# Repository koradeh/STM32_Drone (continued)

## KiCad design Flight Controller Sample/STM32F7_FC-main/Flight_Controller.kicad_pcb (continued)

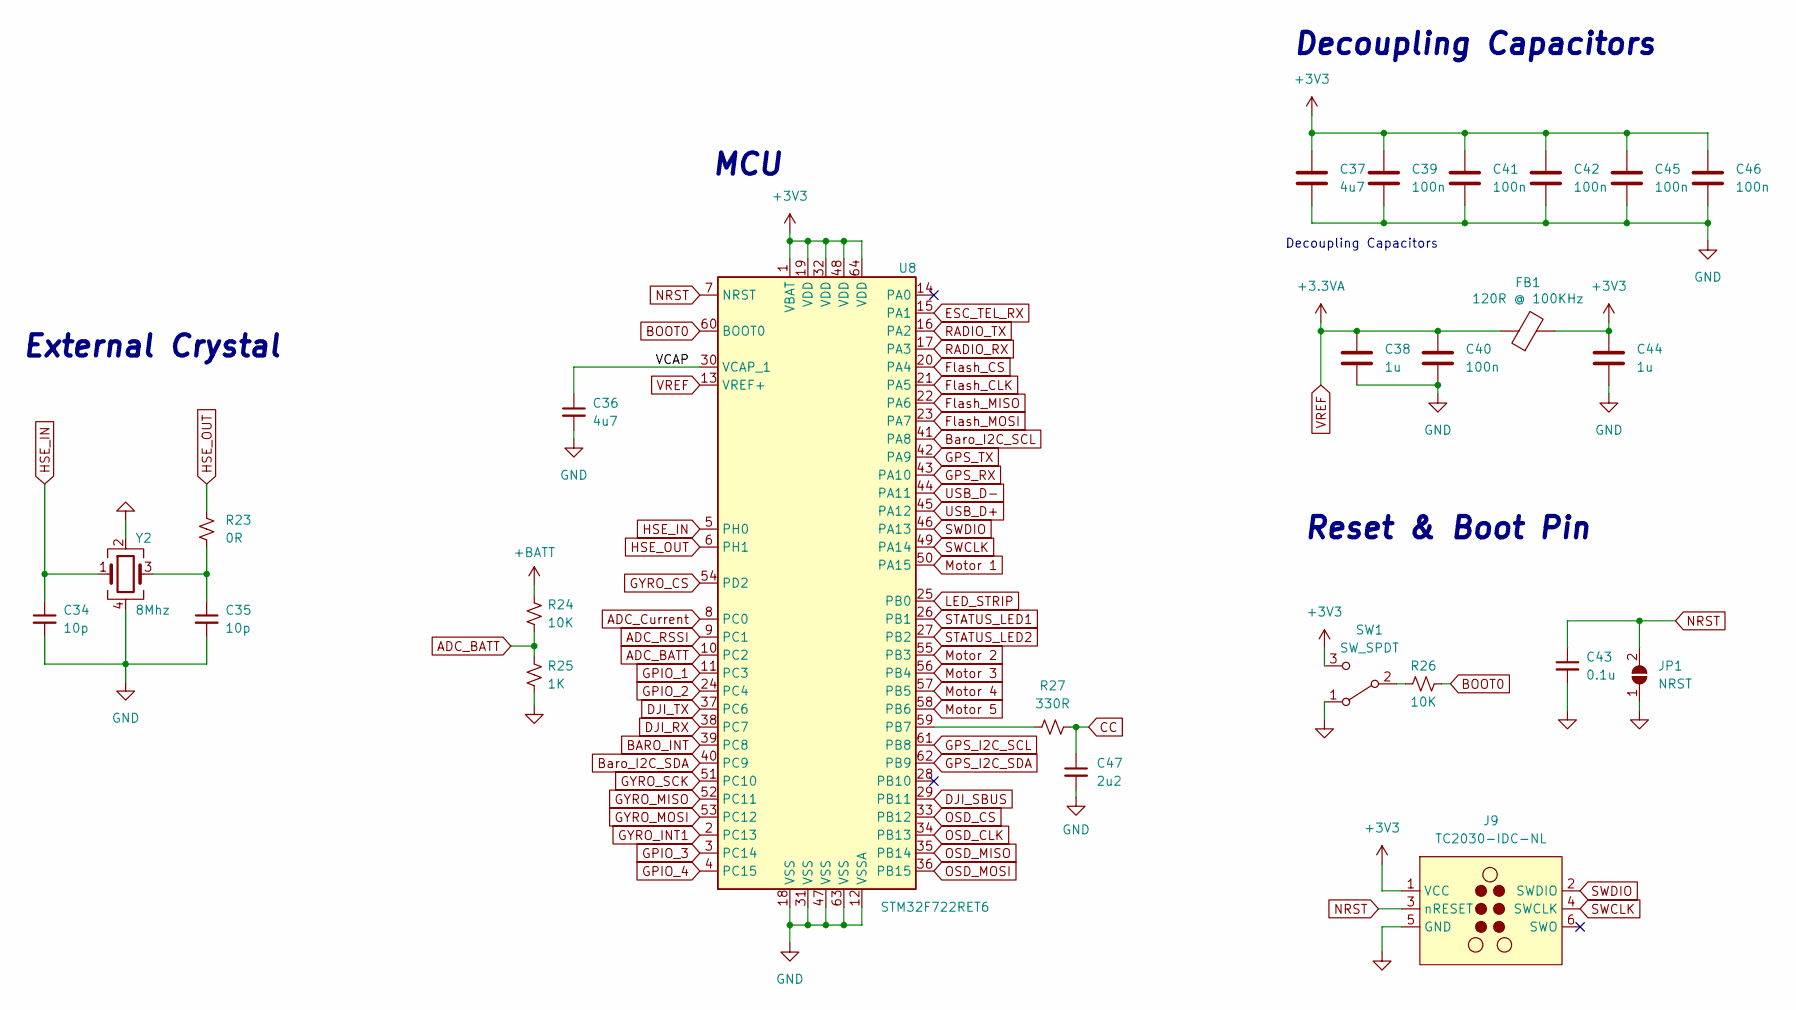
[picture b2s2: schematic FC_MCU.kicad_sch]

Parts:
C34, C35: 10p; C_0402_1005Metric
C36: 4u7; C_0603_1608Metric
C37: 4u7; C_0402_1005Metric
C38, C44: 1u; C_0402_1005Metric
C39, C40, C41, C42, C45, C46: 100n; C_0201_0603Metric
C43: 0.1u; C_0402_1005Metric
C47: 2u2; C_0603_1608Metric
FB1: 120R @ 100KHz; R_0603_1608Metric
J9: TC2030-IDC-NL; Tag-Connect_TC2030-IDC-NL_2x03_P1.27mm_Vertical
JP1: NRST; SolderJumper-2_P1.3mm_Open_TrianglePad1.0x1.5mm
R23: 0R; R_0402_1005Metric
R24: 10K; R_0201_0603Metric
R25: 1K; R_0201_0603Metric
R26: 10K; R_0402_1005Metric
R27: 330R; R_0603_1608Metric
SW1: SW_SPDT; SSSS810701
U8: STM32F722RET6; LQFP-64_10x10mm_P0.5mm
Y2: 8Mhz; Crystal_SMD_3225-4Pin_3.2x2.5mm

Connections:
+3V3: C37.1, C39.1, C41.1, C42.1, C44.1, C45.1, C46.1, FB1.2, J9.1 (VCC), SW1.3 (C), U8.1 (VBAT), U8.19 (VDD), U8.32 (VDD), U8.48 (VDD), U8.64 (VDD); also elsewhere on the board
+BATT: R24.1; also elsewhere on the board
/MCU/VCAP: C36.1, U8.30 (VCAP_1)
ADC_BATT: R24.2, R25.1, U8.10 (PC2)
ADC_Current: U8.8 (PC0); also elsewhere on the board
ADC_RSSI: U8.9 (PC1)
BARO_INT: U8.39 (PC8); also elsewhere on the board
BOOT0: R26.2, U8.60 (BOOT0)
Baro_I2C_SCL: U8.41 (PA8); also elsewhere on the board
Baro_I2C_SDA: U8.40 (PC9); also elsewhere on the board
CC: C47.1, R27.2; also elsewhere on the board
DJI_RX: U8.38 (PC7); also elsewhere on the board
DJI_SBUS: U8.29 (PB11); also elsewhere on the board
DJI_TX: U8.37 (PC6); also elsewhere on the board
ESC_TEL_RX: U8.15 (PA1); also elsewhere on the board
Flash_CLK: U8.21 (PA5); also elsewhere on the board
Flash_CS: U8.20 (PA4); also elsewhere on the board
Flash_MISO: U8.22 (PA6); also elsewhere on the board
Flash_MOSI: U8.23 (PA7); also elsewhere on the board
GND: C34.2, C35.2, C36.2, C37.2, C38.2, C39.2, C40.2, C41.2, C42.2, C43.2, C44.2, C45.2, C46.2, C47.2, J9.5 (GND), JP1.1 (A), R25.2, SW1.1 (A), U8.12 (VSSA), U8.18 (VSS), U8.31 (VSS), U8.47 (VSS), U8.63 (VSS), Y2.2, Y2.4; also elsewhere on the board
GPIO_1: U8.11 (PC3); also elsewhere on the board
GPIO_2: U8.24 (PC4); also elsewhere on the board
GPIO_3: U8.3 (PC14); also elsewhere on the board
GPIO_4: U8.4 (PC15); also elsewhere on the board
GPS_I2C_SCL: U8.61 (PB8); also elsewhere on the board
GPS_I2C_SDA: U8.62 (PB9); also elsewhere on the board
GPS_RX: U8.43 (PA10); also elsewhere on the board
GPS_TX: U8.42 (PA9); also elsewhere on the board
GYRO_CS: U8.54 (PD2); also elsewhere on the board
GYRO_INT1: U8.2 (PC13); also elsewhere on the board
GYRO_MISO: U8.52 (PC11); also elsewhere on the board
GYRO_MOSI: U8.53 (PC12); also elsewhere on the board
GYRO_SCK: U8.51 (PC10); also elsewhere on the board
HSE_IN: C34.1, U8.5 (PH0), Y2.1
HSE_OUT: R23.1, U8.6 (PH1)
LED_STRIP: U8.25 (PB0); also elsewhere on the board
Motor 1: U8.50 (PA15); also elsewhere on the board
Motor 2: U8.55 (PB3); also elsewhere on the board
Motor 3: U8.56 (PB4); also elsewhere on the board
Motor 4: U8.57 (PB5); also elsewhere on the board
Motor 5: U8.58 (PB6); also elsewhere on the board
NRST: C43.1, J9.3 (nRESET), JP1.2 (B), U8.7 (NRST)
unnamed: C35.1, R23.2, Y2.3
unnamed: R26.1, SW1.2 (B)
unnamed: R27.1, U8.59 (PB7)
OSD_CLK: U8.34 (PB13); also elsewhere on the board
OSD_CS: U8.33 (PB12); also elsewhere on the board
OSD_MISO: U8.35 (PB14); also elsewhere on the board
OSD_MOSI: U8.36 (PB15); also elsewhere on the board
RADIO_RX: U8.17 (PA3); also elsewhere on the board
RADIO_TX: U8.16 (PA2); also elsewhere on the board
STATUS_LED1: U8.26 (PB1); also elsewhere on the board
STATUS_LED2: U8.27 (PB2); also elsewhere on the board
SWCLK: J9.4 (SWCLK), U8.49 (PA14)
SWDIO: J9.2 (SWDIO), U8.46 (PA13)
USB_D+: U8.45 (PA12); also elsewhere on the board
USB_D-: U8.44 (PA11); also elsewhere on the board
VREF: C38.1, C40.1, FB1.1, U8.13 (VREF+)

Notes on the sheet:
External Crystal
MCU
Decoupling Capacitors
Reset & Boot Pin

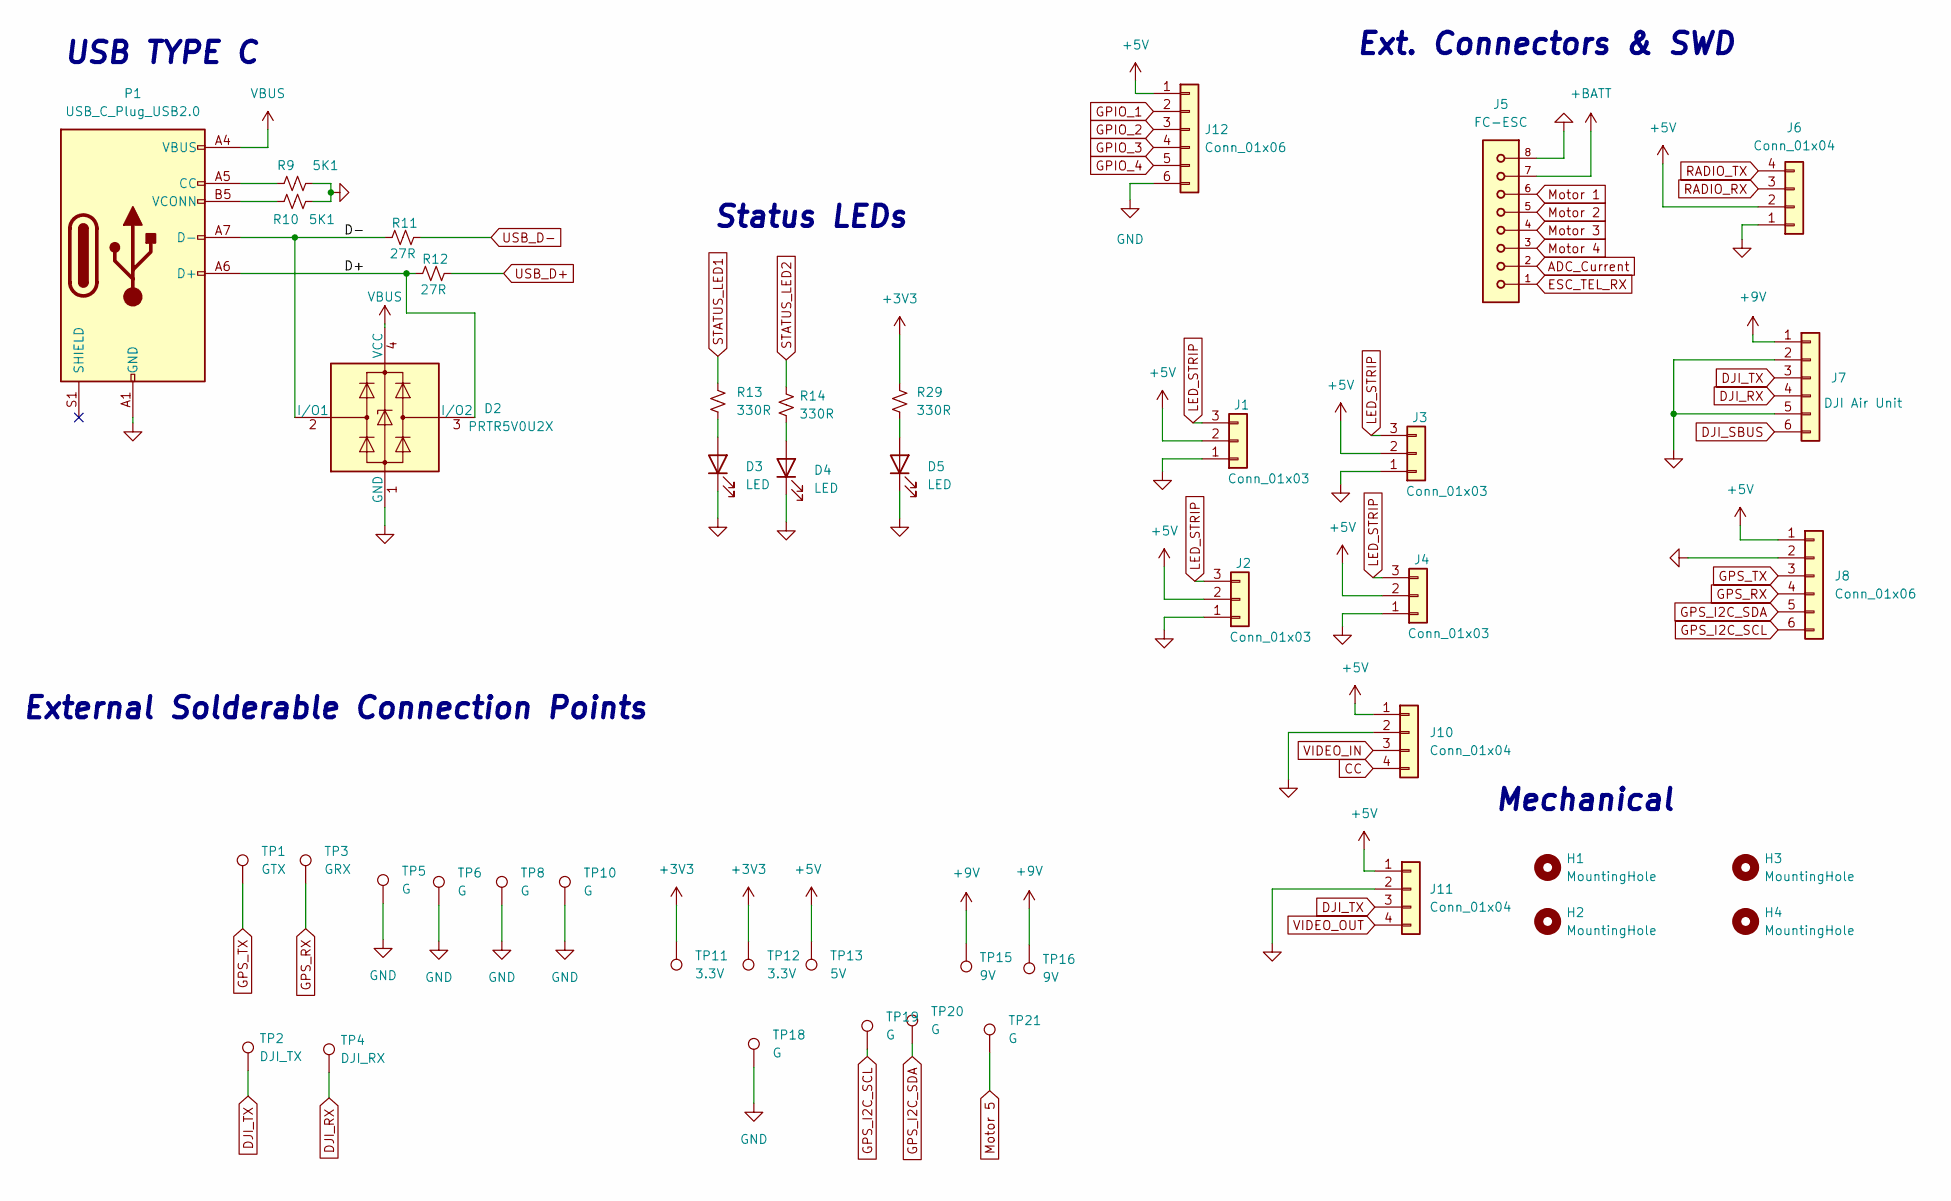
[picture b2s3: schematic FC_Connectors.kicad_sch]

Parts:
D2: PRTR5V0U2X; SOT-143
D3, D4, D5: LED; LED_0402_1005Metric
H1, H2, H3, H4: MountingHole; MountingHole_2.2mm_M2_Pad_Via
J1, J2, J3, J4: Conn_01x03; JST_SH_SM03B-SRSS-TB_1x03-1MP_P1.00mm_Horizontal
J5: FC-ESC; JST_SH_SM08B-SRSS-TB_1x08-1MP_P1.00mm_Horizontal
J6, J10, J11: Conn_01x04; JST_SH_SM04B-SRSS-TB_1x04-1MP_P1.00mm_Horizontal
J7: DJI Air Unit; JST_SH_SM06B-SRSS-TB_1x06-1MP_P1.00mm_Horizontal
J8, J12: Conn_01x06; JST_SH_SM06B-SRSS-TB_1x06-1MP_P1.00mm_Horizontal
P1: USB_C_Plug_USB2.0; USB4110GFA
R9, R10: 5K1; R_0201_0603Metric
R11, R12: 27R; R_0201_0603Metric
R13, R14, R29: 330R; R_0402_1005Metric
TP1: GTX; Solderable Point
TP2: DJI_TX; Solderable Point
TP3: GRX; Solderable Point
TP4: DJI_RX; Solderable Point
TP5, TP6, TP8, TP10, TP18, TP19, TP20, TP21: G; Solderable Point
TP11, TP12: 3.3V; Solderable Point
TP13: 5V; Solderable Point
TP15, TP16: 9V; Solderable Point

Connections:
+3V3: R29.1, TP11.1, TP12.1; also elsewhere on the board
+5V: J1.2, J2.2, J3.2, J4.2, J6.2, J8.1, J10.1, J11.1, J12.1, TP13.1; also elsewhere on the board
+9V: J7.1, TP15.1, TP16.1; also elsewhere on the board
+BATT: J5.7; also elsewhere on the board
/Connectors/D+: D2.3 (I/O2), P1.A6 (D+), R12.1
/Connectors/D-: D2.2 (I/O1), P1.A7 (D-), R11.1
ADC_Current: J5.2; also elsewhere on the board
CC: J10.4; also elsewhere on the board
DJI_RX: J7.4, TP4.1; also elsewhere on the board
DJI_SBUS: J7.6; also elsewhere on the board
DJI_TX: J7.3, J11.3, TP2.1; also elsewhere on the board
ESC_TEL_RX: J5.1; also elsewhere on the board
GND: D2.1 (GND), D3.1 (K), D4.1 (K), D5.1 (K), J1.1, J2.1, J3.1, J4.1, J5.8, J6.1, J7.2, J7.5, J8.2, J10.2, J11.2, J12.6, P1.A1 (GND), P1.A12 (GND), P1.B1 (GND), P1.B12 (GND), R9.1, R10.2, TP5.1, TP6.1, TP8.1, TP10.1, TP18.1; also elsewhere on the board
GPIO_1: J12.2; also elsewhere on the board
GPIO_2: J12.3; also elsewhere on the board
GPIO_3: J12.4; also elsewhere on the board
GPIO_4: J12.5; also elsewhere on the board
GPS_I2C_SCL: J8.6, TP19.1; also elsewhere on the board
GPS_I2C_SDA: J8.5, TP20.1; also elsewhere on the board
GPS_RX: J8.4, TP3.1; also elsewhere on the board
GPS_TX: J8.3, TP1.1; also elsewhere on the board
LED_STRIP: J1.3, J2.3, J3.3, J4.3; also elsewhere on the board
Motor 1: J5.6; also elsewhere on the board
Motor 2: J5.5; also elsewhere on the board
Motor 3: J5.4; also elsewhere on the board
Motor 4: J5.3; also elsewhere on the board
Motor 5: TP21.1; also elsewhere on the board
unnamed: D3.2 (A), R13.2
unnamed: D4.2 (A), R14.2
unnamed: D5.2 (A), R29.2
unnamed: P1.A5 (CC), R9.2
unnamed: P1.B5 (VCONN), R10.1
RADIO_RX: J6.3; also elsewhere on the board
RADIO_TX: J6.4; also elsewhere on the board
STATUS_LED1: R13.1; also elsewhere on the board
STATUS_LED2: R14.1; also elsewhere on the board
USB_D+: R12.2; also elsewhere on the board
USB_D-: R11.2; also elsewhere on the board
VBUS: D2.4 (VCC), P1.A4 (VBUS), P1.A9 (VBUS), P1.B4 (VBUS), P1.B9 (VBUS); also elsewhere on the board
VIDEO_IN: J10.3; also elsewhere on the board
VIDEO_OUT: J11.4; also elsewhere on the board

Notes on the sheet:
USB TYPE C
Status LEDs
Ext. Connectors & SWD
External Solderable Connection Points
Mechanical

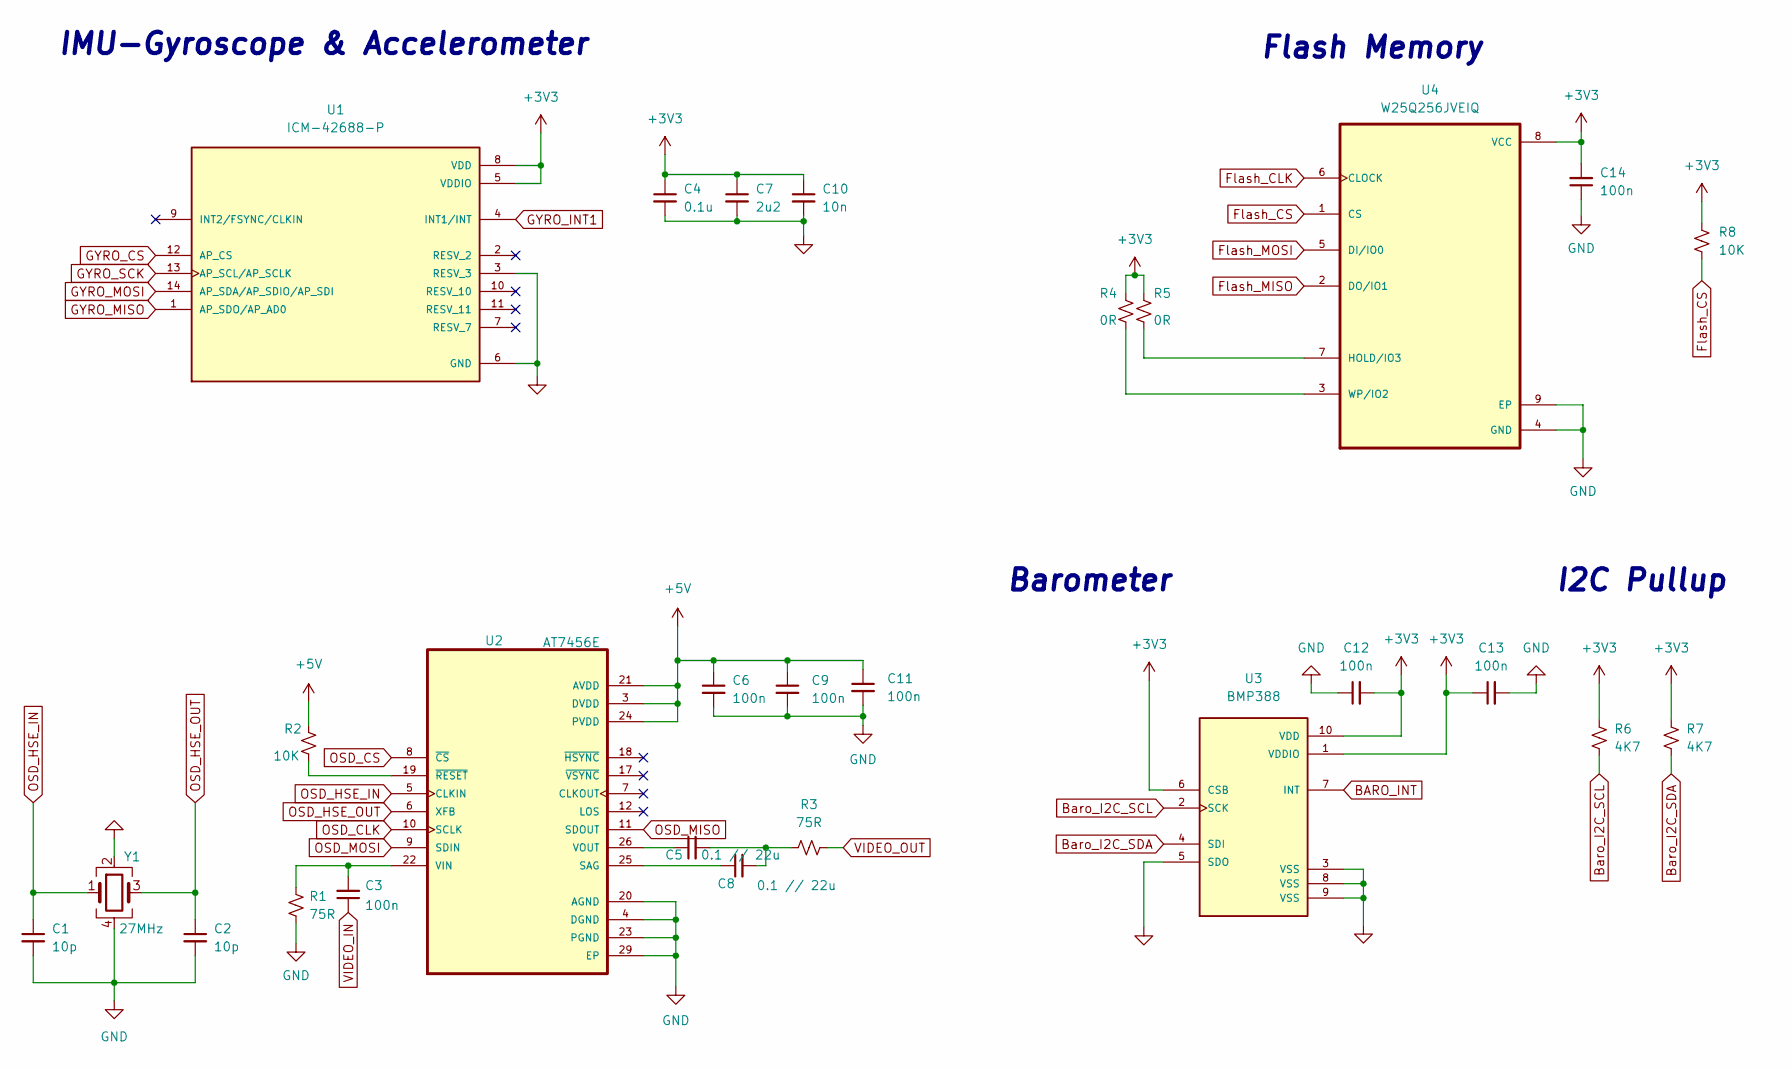
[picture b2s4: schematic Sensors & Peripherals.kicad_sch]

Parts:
C1, C2: 10p; C_0201_0603Metric
C3, C6, C9, C11, C12, C13: 100n; C_0201_0603Metric
C4: 0.1u; C_0402_1005Metric
C5, C8: 0.1 // 22u; C_0201_0603Metric
C7: 2u2; C_0603_1608Metric
C10: 10n; C_0201_0603Metric
C14: 100n; C_0402_1005Metric
R1, R3: 75R; R_0201_0603Metric
R2, R8: 10K; R_0201_0603Metric
R4, R5: 0R; R_0201_0603Metric
R6, R7: 4K7; R_0201_0603Metric
U1: ICM-42688-P; ICP-42688-P; PARTREV 1.2
U2: AT7456E; SOP65P637X110-28N
U3: BMP388; PARTREV 1.1
U4: W25Q256JVEIQ; SON127P600X800X80-9N
Y1: 27MHz; Crystal_SMD_3225-4Pin_3.2x2.5mm

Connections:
+3V3: C4.1, C7.1, C10.1, C12.2, C13.1, C14.2, R4.1, R5.1, R6.1, R7.1, R8.1, U1.5 (VDDIO), U1.8 (VDD), U3.1 (VDDIO), U3.6 (CSB), U3.10 (VDD), U4.8 (VCC); also elsewhere on the board
+5V: C6.1, C9.1, C11.1, R2.2, U2.3 (DVDD), U2.21 (AVDD), U2.24 (PVDD); also elsewhere on the board
BARO_INT: U3.7 (INT); also elsewhere on the board
Baro_I2C_SCL: R6.2, U3.2 (SCK); also elsewhere on the board
Baro_I2C_SDA: R7.2, U3.4 (SDI); also elsewhere on the board
Flash_CLK: U4.6 (CLOCK); also elsewhere on the board
Flash_CS: R8.2, U4.1 (CS); also elsewhere on the board
Flash_MISO: U4.2 (DO/IO1); also elsewhere on the board
Flash_MOSI: U4.5 (DI/IO0); also elsewhere on the board
GND: C1.2, C2.2, C4.2, C6.2, C7.2, C9.2, C10.2, C11.2, C12.1, C13.2, C14.1, R1.2, U1.3 (RESV_3), U1.6 (GND), U2.4 (DGND), U2.20 (AGND), U2.23 (PGND), U2.29 (EP), U3.3 (VSS), U3.5 (SDO), U3.8 (VSS), U3.9 (VSS), U4.4 (GND), U4.9 (EP), Y1.2, Y1.4; also elsewhere on the board
GYRO_CS: U1.12 (AP_CS); also elsewhere on the board
GYRO_INT1: U1.4 (INT1/INT); also elsewhere on the board
GYRO_MISO: U1.1 (AP_SDO/AP_AD0); also elsewhere on the board
GYRO_MOSI: U1.14 (AP_SDA/AP_SDIO/AP_SDI); also elsewhere on the board
GYRO_SCK: U1.13 (AP_SCL/AP_SCLK); also elsewhere on the board
unnamed: C3.2, R1.1, U2.22 (VIN)
unnamed: C5.1, U2.26 (VOUT)
unnamed: C5.2, C8.2, R3.1
unnamed: C8.1, U2.25 (SAG)
unnamed: R2.1, U2.19 (~RESET)
unnamed: R4.2, U4.3 (WP/IO2)
unnamed: R5.2, U4.7 (HOLD/IO3)
OSD_CLK: U2.10 (SCLK); also elsewhere on the board
OSD_CS: U2.8 (~CS); also elsewhere on the board
OSD_HSE_IN: C1.1, U2.5 (CLKIN), Y1.1
OSD_HSE_OUT: C2.1, U2.6 (XFB), Y1.3
OSD_MISO: U2.11 (SDOUT); also elsewhere on the board
OSD_MOSI: U2.9 (SDIN); also elsewhere on the board
VIDEO_IN: C3.1; also elsewhere on the board
VIDEO_OUT: R3.2; also elsewhere on the board

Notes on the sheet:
I2C Pullup
Flash Memory
IMU-Gyroscope & Accelerometer
Barometer

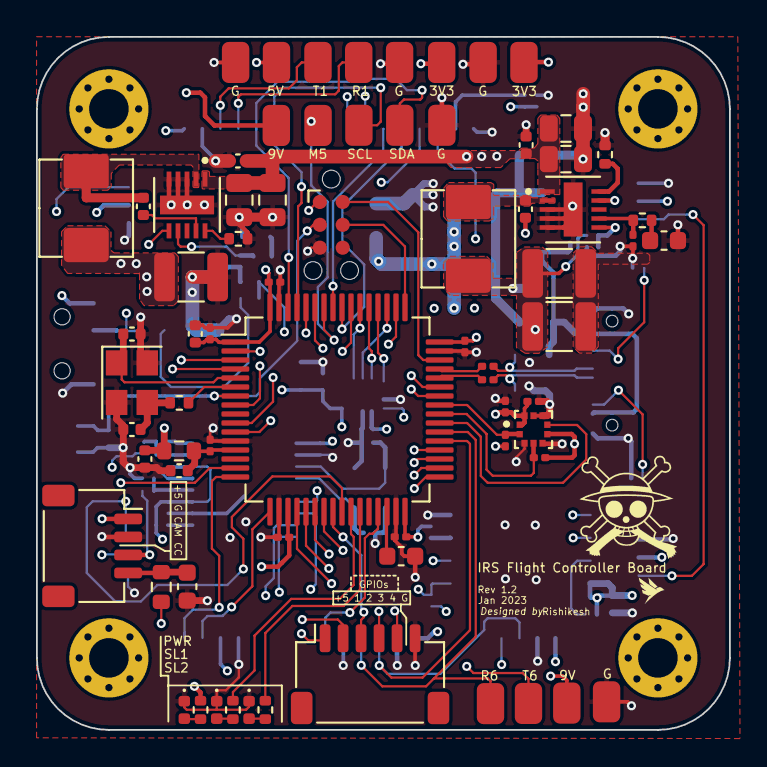
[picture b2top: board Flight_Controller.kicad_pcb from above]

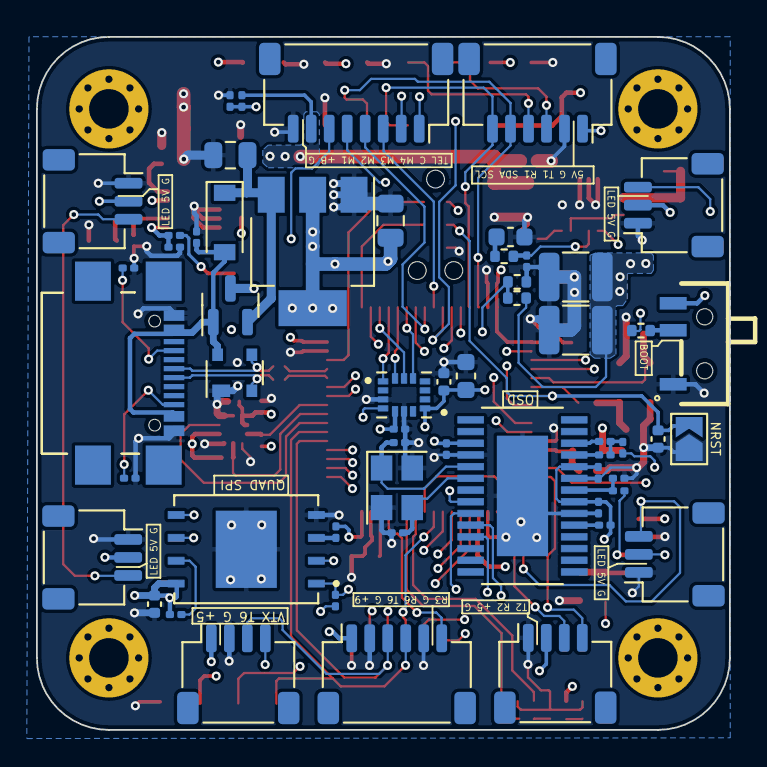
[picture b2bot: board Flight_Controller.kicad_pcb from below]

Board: 8 copper layers, 38.5 x 38.5 mm, 131 parts (56 on the bottom side), 91 nets.

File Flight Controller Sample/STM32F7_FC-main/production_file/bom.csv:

Designator,Footprint,Quantity,Value,LCSC Part #
TP19,Solderable Point,1,G,
TP6,Solderable Point,1,G,
TP5,Solderable Point,1,G,
D3,LED_0402_1005Metric,1,LED,
C39,C_0201_0603Metric,1,100n,
TP4,Solderable Point,1,DJI_RX,
TP8,Solderable Point,1,G,
TP12,Solderable Point,1,3.3V,
TP11,Solderable Point,1,3.3V,
TP10,Solderable Point,1,G,
C46,C_0201_0603Metric,1,100n,
FB1,R_0603_1608Metric,1,120R,
R14,R_0402_1005Metric,1,550R,
H3,MountingHole_2.2mm_M2_Pad_Via,1,MountingHole,
R6,R_0201_0603Metric,1,4K7,
U8,LQFP-64_10x10mm_P0.5mm,1,STM32F722RET6,
TP20,Solderable Point,1,G,
C44,C_0402_1005Metric,1,1u,
TP21,Solderable Point,1,G,
C41,C_0201_0603Metric,1,100n,
C17,C_0805_2012Metric,1,10u,
R18,R_0402_1005Metric,1,10K,
H4,MountingHole_2.2mm_M2_Pad_Via,1,MountingHole,
C38,C_0402_1005Metric,1,1u,
R29,R_0402_1005Metric,1,550R,
L1,MDE0530-6R8M,1,"3u2, IDC 5.4A",
C16,C_0805_2012Metric,1,10u,
C28,C_0603_1608Metric,1,1n8,
C19,C_0805_2012Metric,1,10u,
H1,MountingHole_2.2mm_M2_Pad_Via,1,MountingHole,
C32,C_1210_3225Metric,1,47u,
R27,R_0603_1608Metric,1,330R,
C45,C_0201_0603Metric,1,100n,
TP18,Solderable Point,1,G,
TP13,Solderable Point,1,5V,
R16,R_0402_1005Metric,1,31K,
R15,R_0402_1005Metric,1,31K,
C34,C_0402_1005Metric,1,10p,
D4,LED_0402_1005Metric,1,LED,
R11,R_0201_0603Metric,1,27R,
C12,C_0201_0603Metric,1,100n,
R7,R_0201_0603Metric,1,4K7,
C35,C_0402_1005Metric,1,10p,
TP16,Solderable Point,1,9V,
C13,C_0201_0603Metric,1,100n,
C42,C_0201_0603Metric,1,100n,
J10,JST_SH_SM04B-SRSS-TB_1x04-1MP_P1.00mm_Horizontal,1,Conn_01x04,
TP2,Solderable Point,1,DJI_TX,
R12,R_0201_0603Metric,1,27R,
J9,Tag-Connect_TC2030-IDC-NL_2x03_P1.27mm_Vertical,1,TC2030-IDC-NL,
TP3,Solderable Point,1,GRX,
C30,C_1210_3225Metric,1,47u,
D5,LED_0402_1005Metric,1,LED,
L2,MDE0530-6R8M,1,"2u7, IDC 4A",
H2,MountingHole_2.2mm_M2_Pad_Via,1,MountingHole,
C23,C_0402_1005Metric,1,100n,
TP1,Solderable Point,1,GTX,
C24,C_0402_1005Metric,1,100n,
R13,R_0402_1005Metric,1,550R,
C47,C_0603_1608Metric,1,2u2,
C36,C_0603_1608Metric,1,4u7,
C33,C_1210_3225Metric,1,47u,
C40,C_0201_0603Metric,1,100n,
U7,TPS54335ADRCR,1,TPS54335ADRCR,
C37,C_0402_1005Metric,1,10u,
R23,R_0402_1005Metric,1,0R,
Y2,Crystal_SMD_3225-4Pin_3.2x2.5mm,1,8Mhz,
U6,TPS54335ADRCR,1,TPS54335ADRCR,
TP15,Solderable Point,1,9V,
C21,C_0402_1005Metric,1,100n,
C20,C_0402_1005Metric,1,100n,
C26,C_0201_0603Metric,1,91p,
C18,C_0805_2012Metric,1,10u,
U3,BMP388,1,BMP388,
J12,JST_SH_SM06B-SRSS-TB_1x06-1MP_P1.00mm_Horizontal,1,Conn_01x06,
C10,C_0201_0603Metric,1,10n,
C22,C_0805_2012Metric,1,22u,
C1,C_0201_0603Metric,1,10p,
J5,JST_SH_SM08B-SRSS-TB_1x08-1MP_P1.00mm_Horizontal,1,FC-ESC,
C2,C_0201_0603Metric,1,10p,
R20,R_0402_1005Metric,1,9K7,
R1,R_0201_0603Metric,1,75R,
R5,R_0201_0603Metric,1,0R,
C27,C_0603_1608Metric,1,1n8,
C8,C_0201_0603Metric,1,22u,
J8,JST_SH_SM06B-SRSS-TB_1x06-1MP_P1.00mm_Horizontal,1,Conn_01x06,
Y1,Crystal_SMD_3225-4Pin_3.2x2.5mm,1,27MHz,
R25,R_0201_0603Metric,1,1K,
C15,C_0805_2012Metric,1,10u,
Q1,SOT-23,1,DMG3415,
C3,C_0201_0603Metric,1,100n,
R19,R_0402_1005Metric,1,100K,
U4,SON127P600X800X80-9N,1,W25Q256JVEIQ,
J2,JST_SH_SM03B-SRSS-TB_1x03-1MP_P1.00mm_Horizontal,1,Conn_01x03,
C43,C_0402_1005Metric,1,0.1u,
R3,R_0201_0603Metric,1,75R,
C6,C_0201_0603Metric,1,100n,
R2,R_0201_0603Metric,1,10K,
C5,C_0201_0603Metric,1,22u,
C25,C_0201_0603Metric,1,91p,
R10,R_0201_0603Metric,1,5K1,
SW1,SSSS810701,1,SW_SPDT,
J1,JST_SH_SM03B-SRSS-TB_1x03-1MP_P1.00mm_Horizontal,1,Conn_01x03,
C4,C_0402_1005Metric,1,0.1u,
U5,SOT-223-3_TabPin2,1,AZ1117-ADJ,
J6,JST_SH_SM04B-SRSS-TB_1x04-1MP_P1.00mm_Horizontal,1,Conn_01x04,
C9,C_0201_0603Metric,1,100n,
J3,JST_SH_SM03B-SRSS-TB_1x03-1MP_P1.00mm_Horizontal,1,Conn_01x03,
R22,R_0201_0603Metric,1,19K1,
D1,D_SOD-123,1,RB088LAM-40TFR,
R9,R_0201_0603Metric,1,5K1,
R26,R_0402_1005Metric,1,10K,
C7,C_0603_1608Metric,1,2u2,
R17,R_0402_1005Metric,1,10K,
C29,C_1210_3225Metric,1,47u,
C14,C_0402_1005Metric,1,100n,
C11,C_0201_0603Metric,1,100n,
R24,R_0201_0603Metric,1,10K,
C31,C_1210_3225Metric,1,47u,
J4,JST_SH_SM03B-SRSS-TB_1x03-1MP_P1.00mm_Horizontal,1,Conn_01x03,
J11,JST_SH_SM04B-SRSS-TB_1x04-1MP_P1.00mm_Horizontal,1,Conn_01x04,
R8,R_0201_0603Metric,1,10K,
D2,SOT-143,1,PRTR5V0U2X,
JP1,SolderJumper-2_P1.3mm_Open_TrianglePad1.0x1.5mm,1,NRST,
U2,SOP65P637X110-28N,1,AT7456E,
R21,R_0201_0603Metric,1,100K,
J7,JST_SH_SM06B-SRSS-TB_1x06-1MP_P1.00mm_Horizontal,1,DJI Air Unit,
P1,USB4110GFA,1,USB_C_Plug_USB2.0,
R4,R_0201_0603Metric,1,0R,
R28,R_0201_0603Metric,1,100K,
U1,ICP-42688-P,1,ICM-42688-P,

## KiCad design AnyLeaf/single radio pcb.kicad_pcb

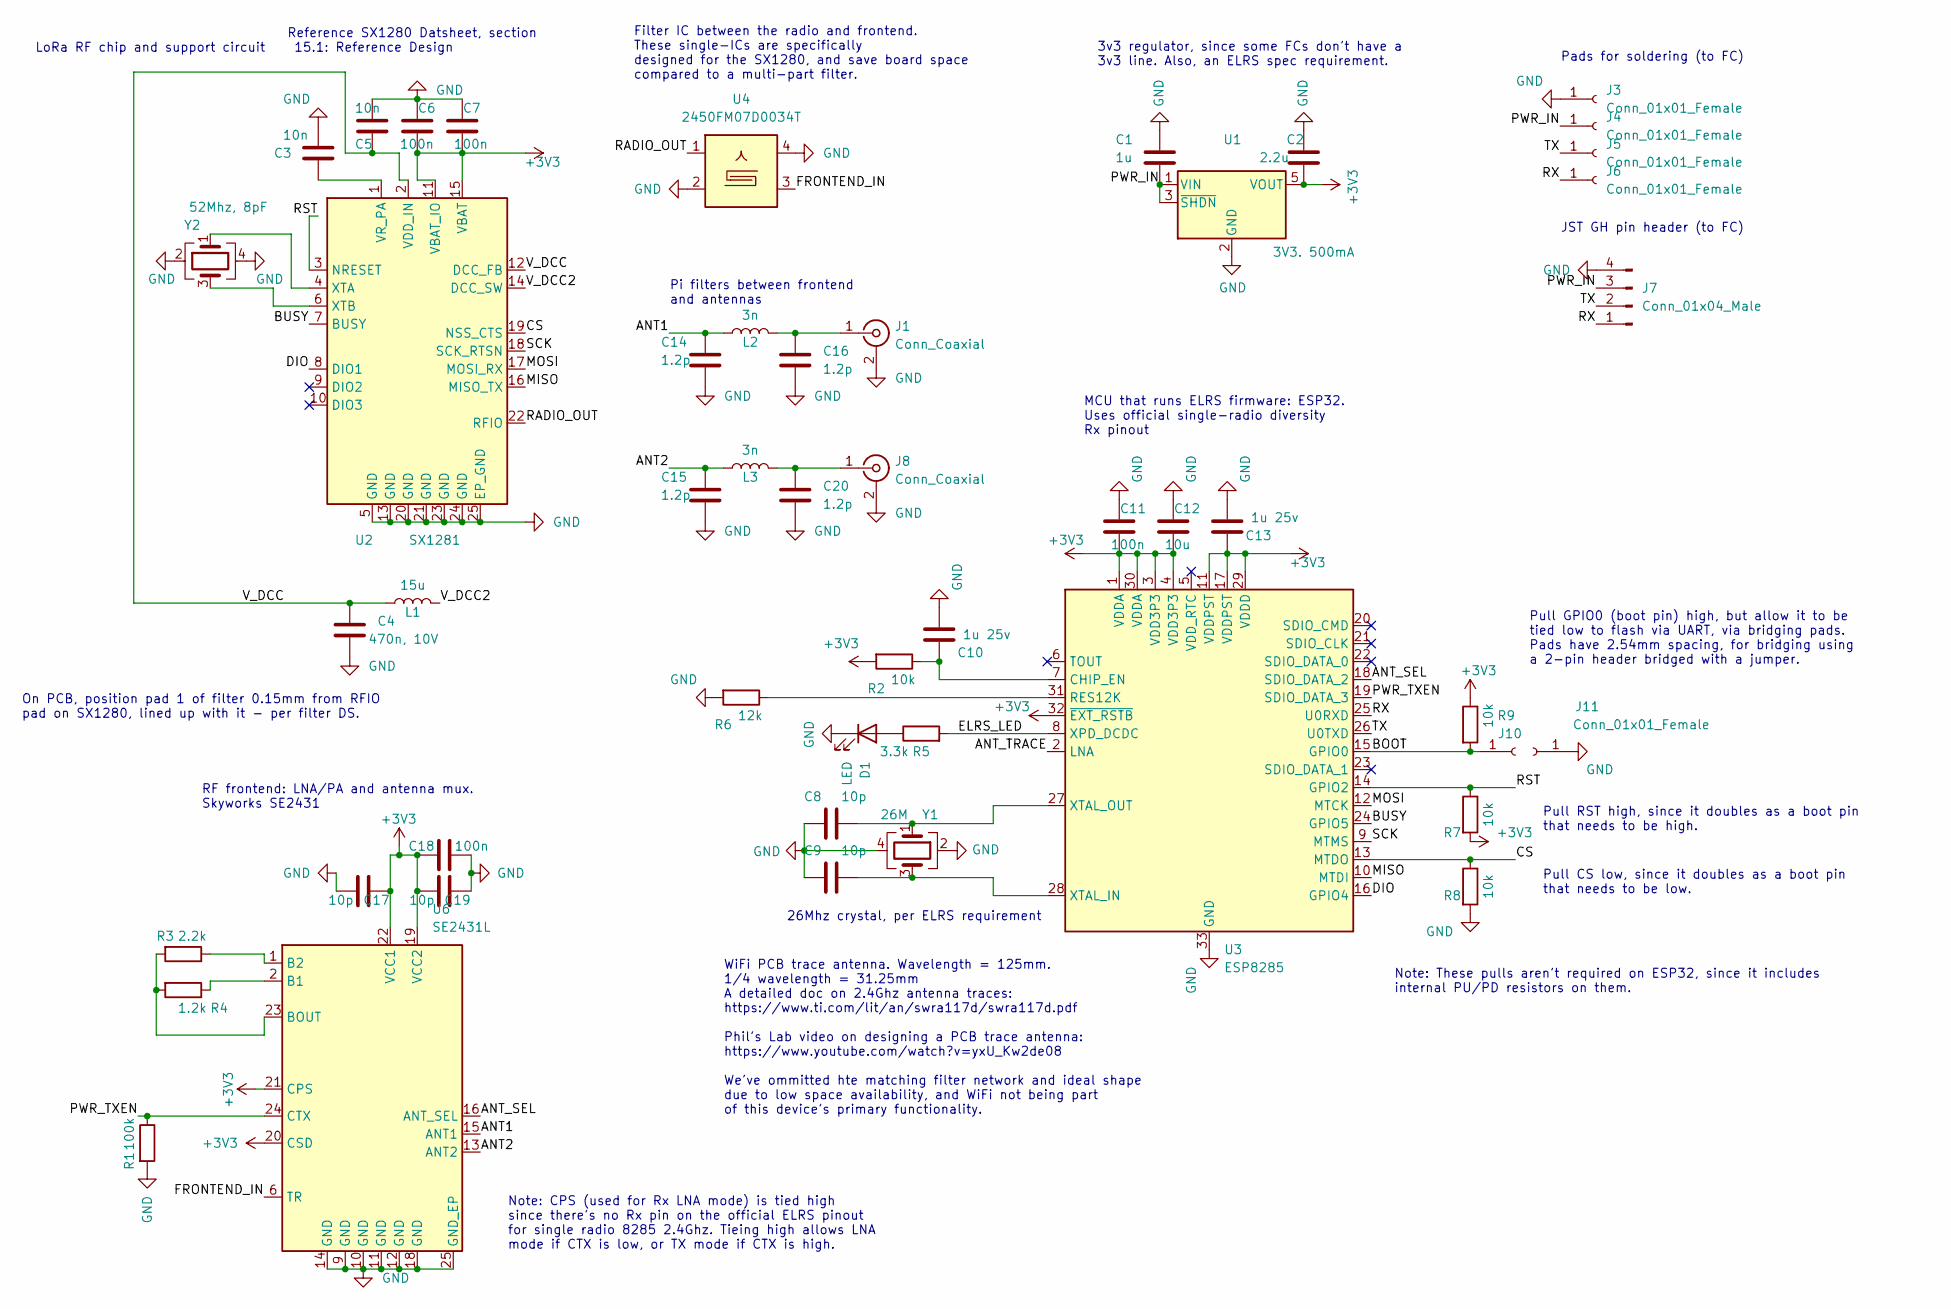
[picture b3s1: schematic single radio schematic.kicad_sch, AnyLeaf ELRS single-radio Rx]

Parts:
C1: 1u; C_0402_1005Metric; LCSC C52923
C2: 2.2u; C_0402_1005Metric; LCSC C12530
C3, C5: 10n; C_0402_1005Metric; LCSC C15195
C4: 470n, 10V; C_0402_1005Metric; LCSC C47339
C6, C7, C11, C18: 100n; C_0402_1005Metric; LCSC C1525
C8, C9, C17, C19: 10p; C_0402_1005Metric; LCSC C32949
C10, C13: 1u 25v; C_0402_1005Metric; LCSC C52923
C12: 10u; C_0402_1005Metric; LCSC C15525
C14, C15, C16, C20: 1.2p; C_0402_1005Metric; LCSC C327292
D1: LED; LED_0603_1608Metric; LCSC C2286
J1, J8: Conn_Coaxial; U.FL_Hirose_U.FL-R-SMT-1_Vertical; Part Hirose U.FL-R-SMT-1(80); LCSC C88374
J3, J4, J5, J6: Conn_01x01_Female; TestPoint_Pad_2.5x2.5mm
J7: Conn_01x04_Male; JST_GH_SM04B-GHS-TB_1x04-1MP_P1.25mm_Horizontal; LCSC C189895
J10, J11: Conn_01x01_Female; TestPoint_Pad_1.0x1.0mm
L1: 15u; L_0805_2012Metric; LCSC C486333
L2, L3: 3n; L_0402_1005Metric; LCSC C269824
R1: 100k; R_0402_1005Metric; LCSC C25741
R2, R7, R8, R9: 10k; R_0402_1005Metric; LCSC C25744
R3: 2.2k; R_0402_1005Metric; LCSC C25879
R4: 1.2k; R_0402_1005Metric; LCSC C25862
R5: 3.3k; R_0402_1005Metric; LCSC C25890
R6: 12k; R_0402_1005Metric; LCSC C25752
U1: 3V3. 500mA; TSOT-23-5; Part TPRT9013-33GB; LCSC C587158
U2: SX1281; QFN-24-1EP_4x4mm_P0.5mm_EP2.6x2.6mm; Digikey SX1281IMLTRTTR-ND
U3: ESP8285; QFN-32-1EP_5x5mm_P0.5mm_EP3.45x3.45mm; LCSC C967019
U4: 2450FM07D0034T; 2450FM07D0034; Mouser 609-2450FM07D0034T
U6: SE2431L; QFN-24-1EP_3x4mm_P0.4mm_EP1.65x2.65mm; Digikey 863-1347-2-ND
Y1: 26M; Crystal_SMD_2016-4Pin_2.0x1.6mm; LCSC C843259
Y2: 52Mhz, 8pF; Crystal_SMD_2016-4Pin_2.0x1.6mm; LCSC C781783

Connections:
+3V3: C2.2, C6.2, C7.2, C11.2, C12.2, C13.1, C17.2, C18.1, C19.1, R2.2, R7.2, R9.1, U1.5 (VOUT), U2.11 (VBAT_IO), U2.15 (VBAT), U3.1 (VDDA), U3.3 (VDD3P3), U3.4 (VDD3P3), U3.11 (VDDPST), U3.17 (VDDPST), U3.29 (VDDD), U3.30 (VDDA), U3.32 (~EXT_RSTB), U6.19 (VCC2), U6.20 (CSD), U6.21 (CPS), U6.22 (VCC1)
/ANT1: C14.1, L2.1, U6.15 (ANT1)
/ANT2: C15.1, L3.1, U6.13 (ANT2)
/ANT_SEL: U3.18 (SDIO_DATA_2), U6.16 (ANT_SEL)
/ANT_TRACE: U3.2 (LNA)
/BOOT: J10.1, R9.2, U3.15 (GPIO0)
/BUSY: U2.7 (BUSY), U3.24 (GPIO5)
/CS: R8.1, U2.19 (NSS_CTS), U3.13 (MTDO)
/DIO: U2.8 (DIO1), U3.16 (GPIO4)
/ELRS_LED: R5.2, U3.8 (XPD_DCDC)
/FRONTEND_IN: U4.3, U6.6 (TR)
/MISO: U2.16 (MISO_TX), U3.10 (MTDI)
/MOSI: U2.17 (MOSI_RX), U3.12 (MTCK)
/PWR_IN: C1.2, J4.1, J7.3, U1.1 (VIN), U1.3 (~SHDN)
/PWR_TXEN: R1.1, U3.19 (SDIO_DATA_3), U6.24 (CTX)
/RADIO_OUT: U2.22 (RFIO), U4.1
/RST: R7.1, U2.3 (NRESET), U3.14 (GPIO2)
/RX: J6.1, J7.1, U3.25 (U0RXD)
/SCK: U2.18 (SCK_RTSN), U3.9 (MTMS)
/TX: J5.1, J7.2, U3.26 (U0TXD)
/V_DCC: C4.1, C5.2, L1.1, U2.2 (VDD_IN), U2.12 (DCC_FB)
/V_DCC2: L1.2, U2.14 (DCC_SW)
GND: C1.1, C2.1, C3.1, C4.2, C5.1, C6.1, C7.1, C8.1, C9.1, C10.2, C11.1, C12.1, C13.2, C14.2, C15.2, C16.2, C17.1, C18.2, C19.2, C20.2, D1.1 (K), J1.2 (Ext), J3.1, J7.4, J8.2 (Ext), J11.1, R1.2, R6.2, R8.2, U1.2 (GND), U2.5 (GND), U2.13 (GND), U2.20 (GND), U2.21 (GND), U2.23 (GND), U2.24 (GND), U2.25 (EP_GND), U3.33 (GND), U4.2, U4.4, U4.5, U6.9 (GND), U6.10 (GND), U6.11 (GND), U6.12 (GND), U6.14 (GND), U6.18 (GND), U6.25 (GND_EP), Y1.2, Y1.4, Y2.2, Y2.4
unnamed: C3.2, U2.1 (VR_PA)
unnamed: C8.2, U3.27 (XTAL_OUT), Y1.1
unnamed: C9.2, U3.28 (XTAL_IN), Y1.3
unnamed: C10.1, R2.1, U3.7 (CHIP_EN)
unnamed: C16.1, J1.1 (In), L2.2
unnamed: C20.1, J8.1 (In), L3.2
unnamed: D1.2 (A), R5.1
unnamed: R3.1, U6.1 (B2)
unnamed: R3.2, R4.2, U6.23 (BOUT)
unnamed: R4.1, U6.2 (B1)
unnamed: R6.1, U3.31 (RES12K)
unnamed: U2.4 (XTA), Y2.1
unnamed: U2.6 (XTB), Y2.3

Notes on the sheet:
26Mhz crystal, per ELRS requirement
MCU that runs ELRS firmware: ESP32. Uses official single-radio diversity Rx pinout
JST GH pin header (to FC)
Note: These pulls aren't required on ESP32, since it includes internal PU/PD resistors on them.
Pi filters between frontend and antennas
Pads for soldering (to FC)
Note: CPS (used for Rx LNA mode) is tied high since there's no Rx pin on the official ELRS pinout for single radio 8285 2.4Ghz. Tieing high allows LNA mode if CTX is low, or TX mode if CTX is high.
3v3 regulator, since some FCs don't have a 3v3 line. Also, an ELRS spec requirement.
WiFi PCB trace antenna. Wavelength = 125mm. 1/4 wavelength = 31.25mm A detailed doc on 2.4Ghz antenna traces: https://www.ti.com/lit/an/swra117d/swra117d.pdf Phil's Lab video on designing a PCB trace antenna: https://www.youtube.com/watch?v=yxU_Kw2de08 We've ommitted hte matching filter network and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
Pull CS low, since it doubles as a boot pin that needs to be low.
Reference SX1280 Datsheet, section 15.1: Reference Design
RF frontend: LNA/PA and antenna mux. Skyworks SE2431
Pull GPIO0 (boot pin) high, but allow it to be tied low to flash via UART, via bridging pads. Pads have 2.54mm spacing, for bridging using a 2-pin header bridged with a jumper.
On PCB, position pad 1 of filter 0.15mm from RFIO pad on SX1280, lined up with it - per filter DS.
Pull RST high, since it doubles as a boot pin that needs to be high.
LoRa RF chip and support circuit
Filter IC between the radio and frontend. These single-ICs are specifically designed for the SX1280, and save board space compared to a multi-part filter.

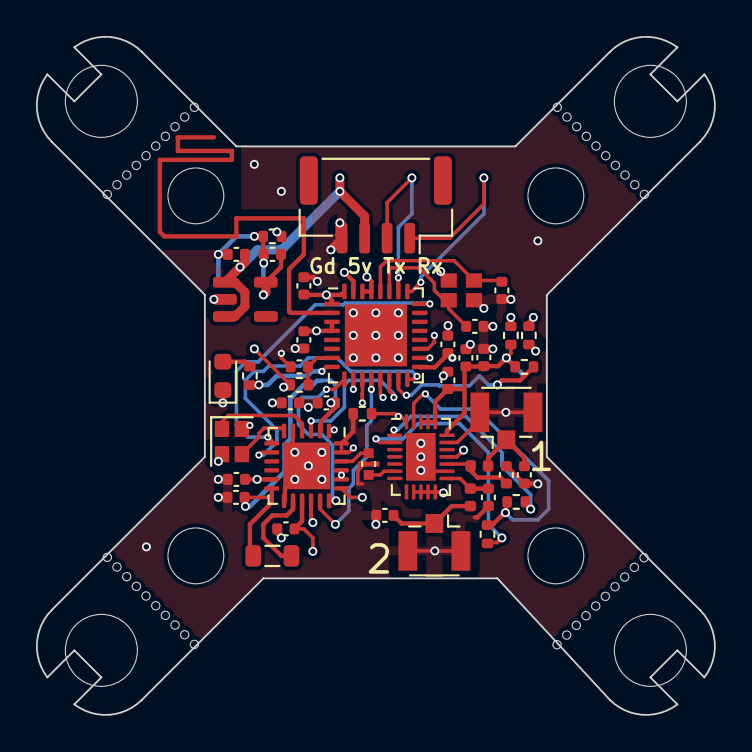
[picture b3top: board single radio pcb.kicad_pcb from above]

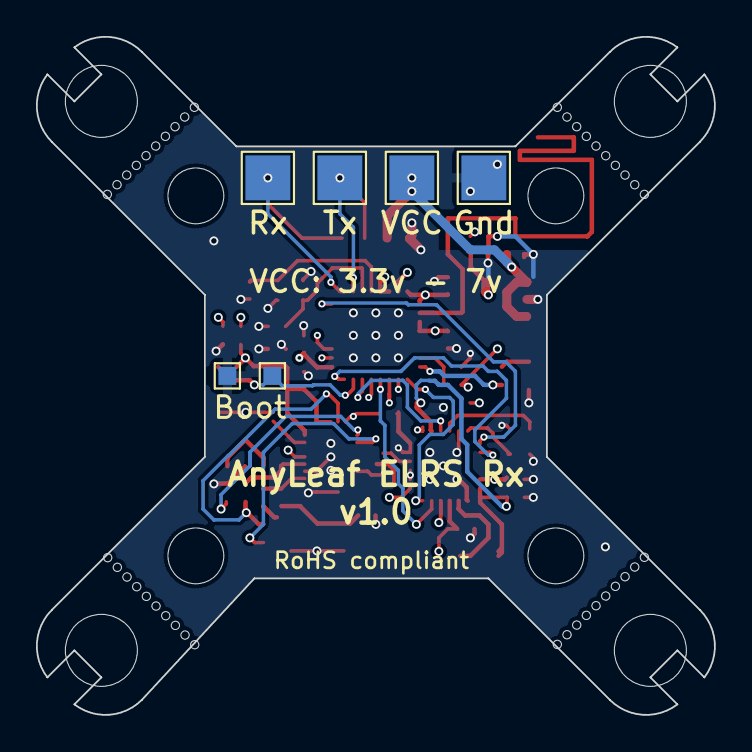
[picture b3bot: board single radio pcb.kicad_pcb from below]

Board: 4 copper layers, 37.7 x 37.7 mm, 61 parts (6 on the bottom side), 35 nets.

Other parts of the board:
H1, H2, H3, H4, H7, H8, H9, H10: MountingHole; MountingHole_3.2mm_M3
H5, H6, H11, H12: MountingHole_Pad; Mouse bites_7mm

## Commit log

2025-04-08 Completed Flight Controller PCB (ZenFlyF7 version 2)
